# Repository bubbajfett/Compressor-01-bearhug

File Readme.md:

Pedal PCB based on Bearhug compressor.

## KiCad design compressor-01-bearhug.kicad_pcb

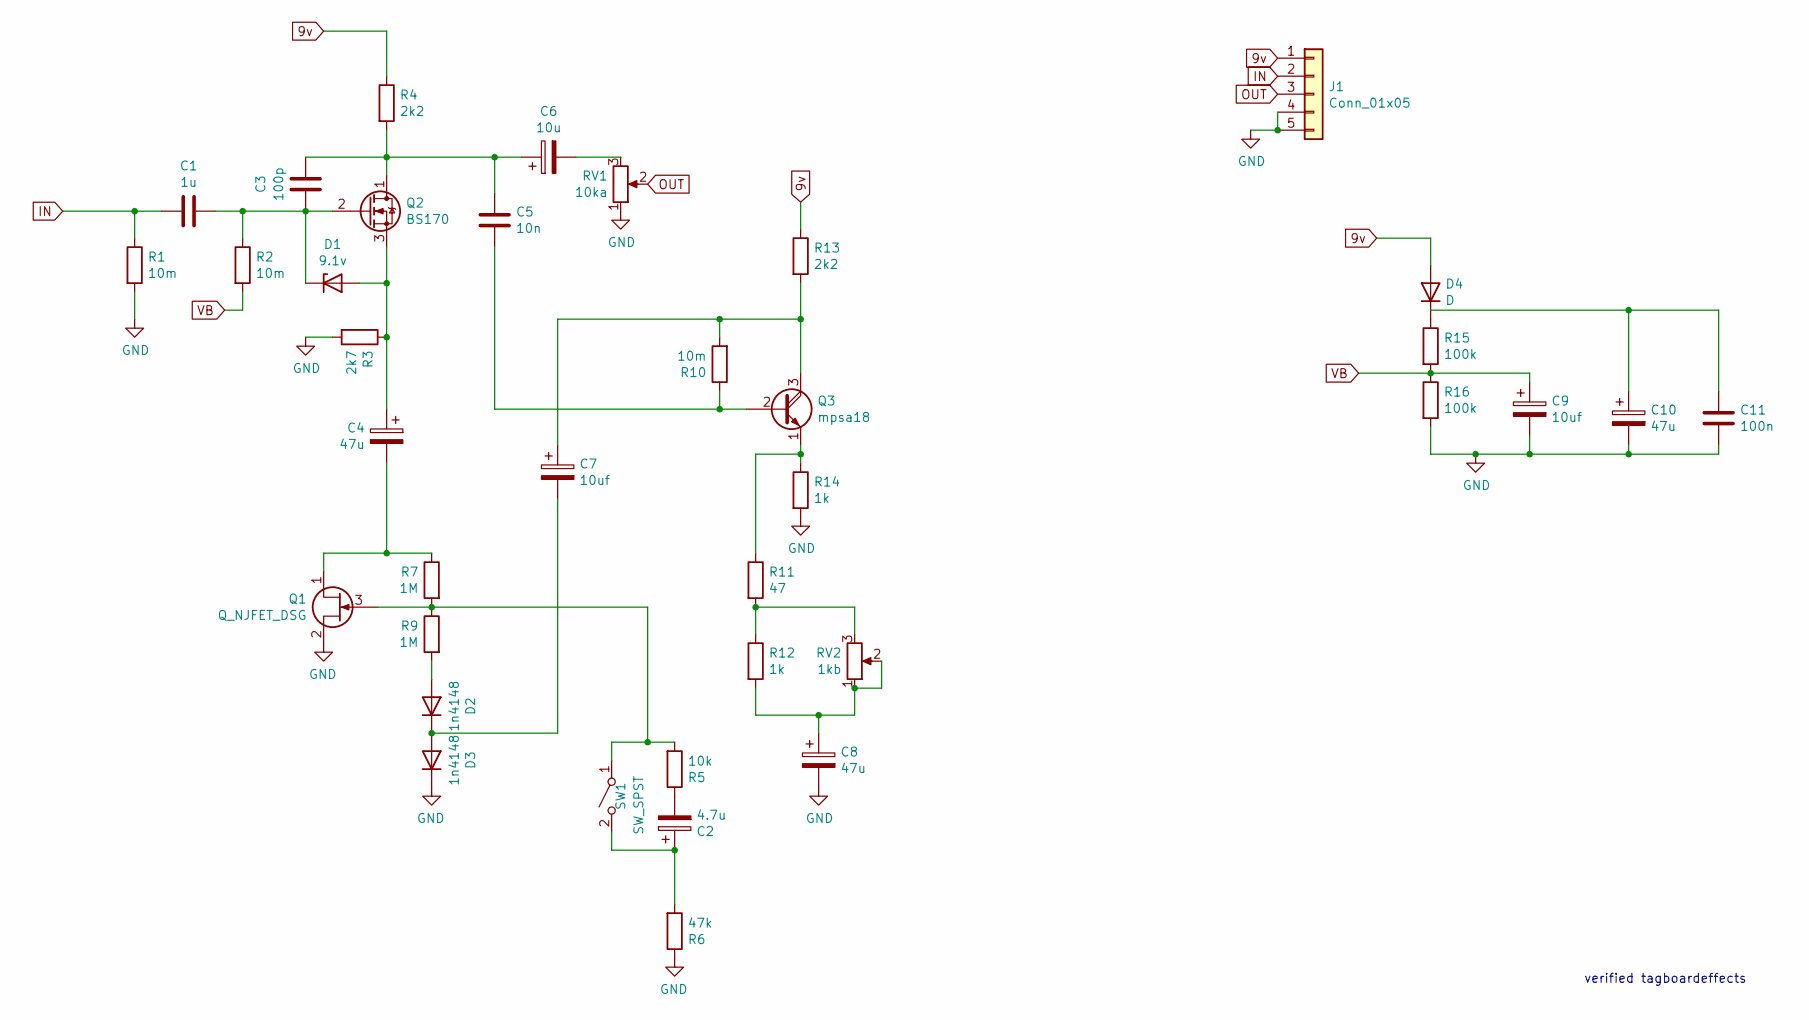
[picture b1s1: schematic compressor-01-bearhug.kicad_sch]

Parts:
C1: 1u; C_Disc_D7.5mm_W2.5mm_P5.00mm
C2: 4.7u; CP_Radial_D6.3mm_P2.50mm
C3: 100p; C_Disc_D7.5mm_W2.5mm_P5.00mm
C4, C8, C10: 47u; CP_Radial_D7.5mm_P2.50mm
C5: 10n; C_Disc_D7.5mm_W2.5mm_P5.00mm
C6: 10u; CP_Radial_D7.5mm_P2.50mm
C7, C9: 10uf; CP_Radial_D6.3mm_P2.50mm
C11: 100n; C_Disc_D7.5mm_W2.5mm_P5.00mm
D1: 9.1v; D_A-405_P7.62mm_Horizontal
D2, D3: 1n4148; D_A-405_P7.62mm_Horizontal
D4: D; D_A-405_P7.62mm_Horizontal
J1: Conn_01x05; PinHeader_1x05_P2.54mm_Vertical
Q1: Q_NJFET_DSG; TO-92_Inline
Q2: BS170; TO-92_Inline
Q3: mpsa18; TO-92_Inline
R1, R2, R10: 10m; R_Axial_DIN0207_L6.3mm_D2.5mm_P7.62mm_Horizontal
R3: 2k7; R_Axial_DIN0207_L6.3mm_D2.5mm_P7.62mm_Horizontal
R4, R13: 2k2; R_Axial_DIN0207_L6.3mm_D2.5mm_P7.62mm_Horizontal
R5: 10k; R_Axial_DIN0207_L6.3mm_D2.5mm_P7.62mm_Horizontal
R6: 47k; R_Axial_DIN0207_L6.3mm_D2.5mm_P7.62mm_Horizontal
R7, R9: 1M; R_Axial_DIN0207_L6.3mm_D2.5mm_P7.62mm_Horizontal
R11: 47; R_Axial_DIN0207_L6.3mm_D2.5mm_P7.62mm_Horizontal
R12, R14: 1k; R_Axial_DIN0207_L6.3mm_D2.5mm_P7.62mm_Horizontal
R15, R16: 100k; R_Axial_DIN0207_L6.3mm_D2.5mm_P7.62mm_Horizontal
RV1: 10ka; SolderWirePad_1x03_P4.445mm_Drill1.5mm
RV2: 1kb; SolderWirePad_1x03_P4.445mm_Drill1.5mm
SW1: SW_SPST; PinHeader_1x03_P2.54mm_Vertical

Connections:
9v: D4.2 (A), J1.1, R4.1, R13.1
GND: C8.2, C9.2, C10.2, C11.2, D3.1 (K), J1.4, J1.5, Q1.2 (S), R1.2, R3.2, R6.1, R14.2, R16.2, RV1.1
IN: C1.2, J1.2, R1.1
unnamed: C1.1, C3.1, D1.1 (K), Q2.2 (G), R2.1
unnamed: C2.1, R6.2, SW1.2 (B)
unnamed: C2.2, R5.1
unnamed: C3.2, C5.1, C6.1, Q2.1 (D), R4.2
unnamed: C4.1, D1.2 (A), Q2.3 (S), R3.1
unnamed: C4.2, Q1.1 (D), R7.1
unnamed: C5.2, Q3.2 (B), R10.1
unnamed: C6.2, RV1.3
unnamed: C7.1, Q3.3 (C), R10.2, R13.2
unnamed: C7.2, D2.1 (K), D3.2 (A)
unnamed: C8.1, R12.2, RV2.1, RV2.2
unnamed: C10.1, C11.1
unnamed: D2.2 (A), R9.2
unnamed: D4.1 (K), R15.1
unnamed: Q1.3 (G), R5.2, R7.2, R9.1, SW1.1 (A)
unnamed: Q3.1 (E), R11.1, R14.1
unnamed: R11.2, R12.1, RV2.3
OUT: J1.3, RV1.2
VB: C9.1, R2.2, R15.2, R16.1

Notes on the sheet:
verified tagboardeffects

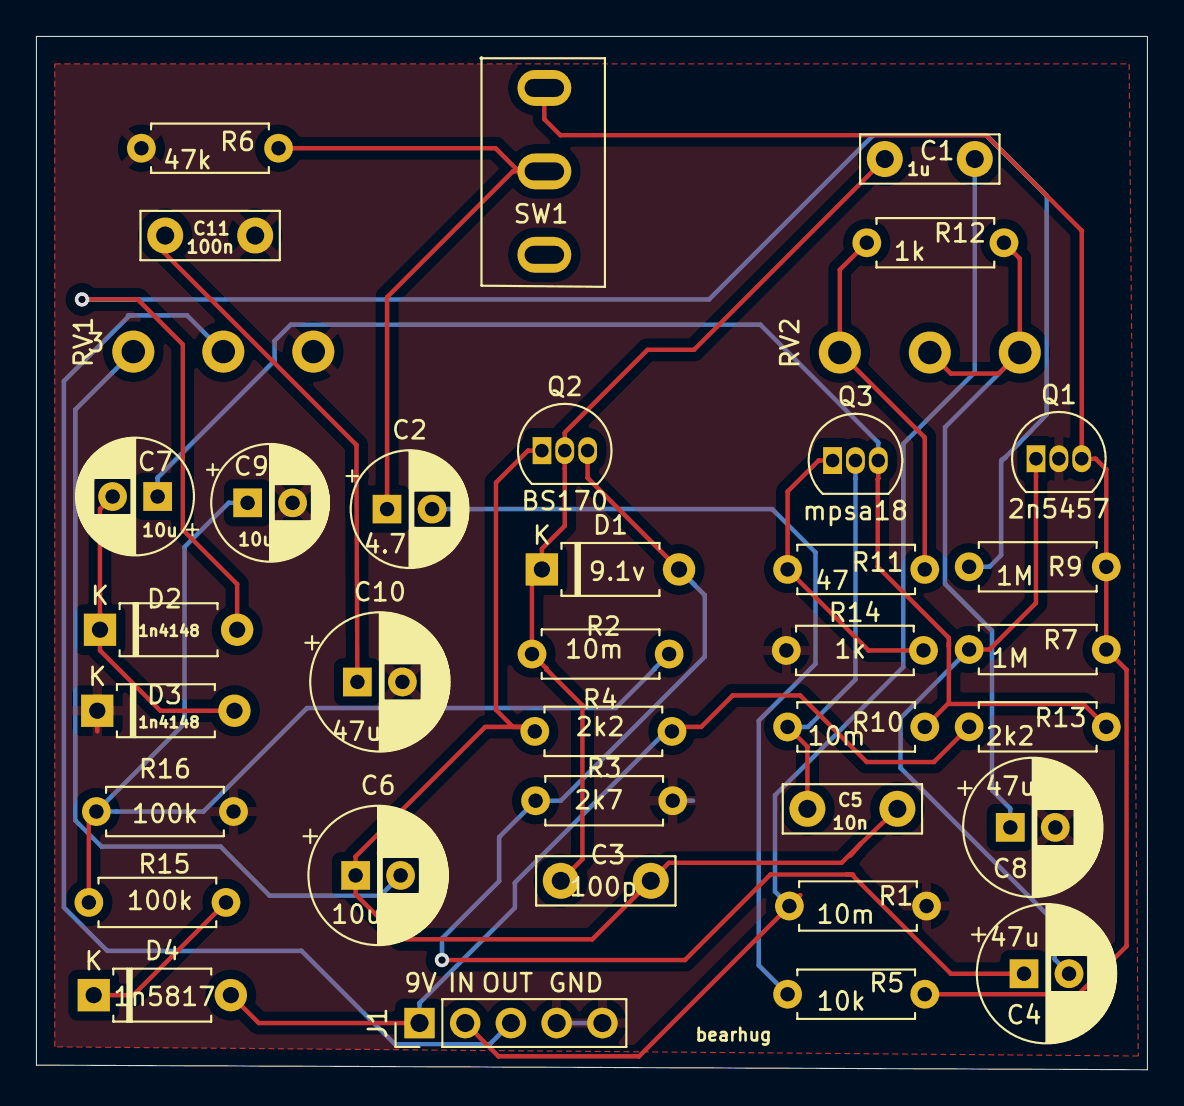
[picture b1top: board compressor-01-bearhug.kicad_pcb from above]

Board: 2 copper layers, 61.7 x 57.4 mm, 37 parts (0 on the bottom side), 22 nets.

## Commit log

2026-02-03 bug in schematic caused missing connection to the power filter caps
2026-02-06 added license
